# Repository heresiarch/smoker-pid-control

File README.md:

# smoker-pid-control
Arduino based PID Controller with PT1000 elements to control heat in BBQ grill using a blower fan
* PWM Output 0-255 
* Manual controller mode
* PID based controller mode
* Fuzzy based controller mode
* OLED Display
* Adafruit MAX31865 RTD Sensor Breakout module
* Arduino Micro
* Rotary Encoder user interface

# Field Test
## PID Mode
PID Mode works very well with Weber 57 cm BBQ Grill. Only small overshots in the beginning. I use a BBQ Guru Viper Pit 12 V Fan which has no PWM, PWM is converted to linear voltage with a simple Buck converter. PID Values are very much dependend on the type of BBQ Grill. I have a hard cut off rule above 1.0 °C which counters some overshots in the beginning. Autotune experiments are a good waste of time IMHO, better is to use PID values based on experiments. 

## Fuzzy Mode
Fuzzy mode is very stable and gets good steady state for setpoint temperature. Fuzzy mode is controlled by Fuzzyset based on temperature difference. You should change rules sets based on your setup and used MOSFET (RDSon and PWM values). Fuzzy update rate is 5 seconds. I derived a simple fuzzy set from the much more sophisticated example from the link below, which has unfortunately too many rules for my Arduino Micro memory: https://github.com/rvt/bbq-controller/blob/master/lib/bbq/bbqfanonly.cpp.

## Results
Overall I could hold constant temperature of 110 °C over 4 hours with 1 char basket filled with some weber charcoal briquettes, and still had enough of them left for some hours. With 2 char baskets starting on each side with 2-3 hot coals in ignition cord style and with grill fully meat loaded I got superior results in temperature stability with the Fuzzy Sets defined.

## References and similar Projects
* [Smokerduino on Instructables](https://www.instructables.com/id/Smokerduino/)
* [Fuzzy based BBQ Controler Project](https://github.com/rvt/bbq-controller)
* [Small OLED Library ss_oled](https://github.com/bitbank2/ss_oled)
* [Another small OLED Library SSD1306Ascii](https://github.com/greiman/SSD1306Ascii)

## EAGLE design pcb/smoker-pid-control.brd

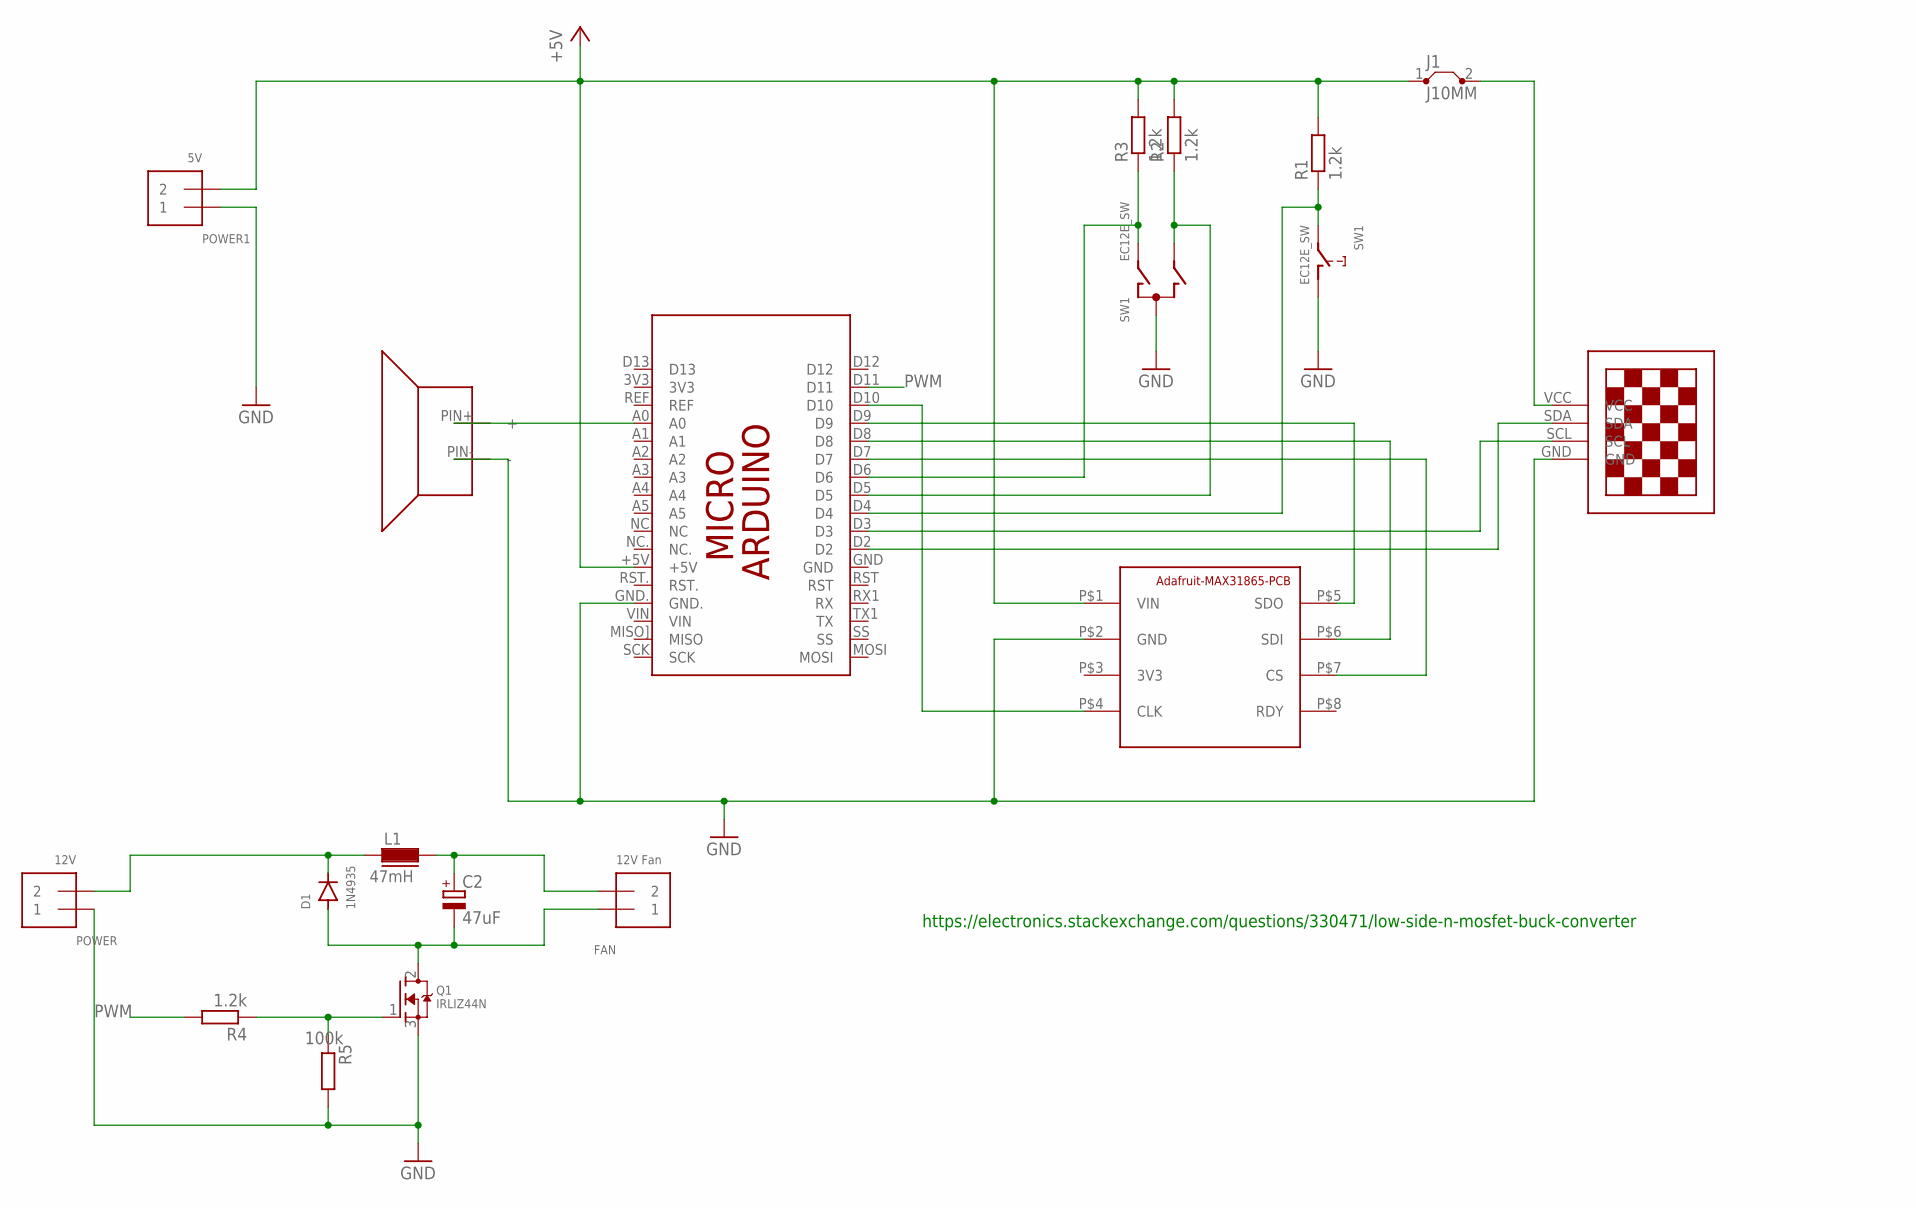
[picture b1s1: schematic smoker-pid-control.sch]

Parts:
C2: 47uF; E5-8,5
D1: 1N4935; DO34-7
FAN: 12V Fan; TERMBLOCK_1X2-3.5MM
J1: J10MM; 10
L1: 47mH; FASTRON_07HCP_INDUCTOR
PCB1: ARDUINO_MICRO
POWER: 12V; TERMBLOCK_1X2-3.5MM
POWER1: 5V; TERMBLOCK_1X2-3.5MM
Q1: IRLIZ44N; TO220V
R1, R3, R4: 1.2k; 0207/10
R2: 1.2k; 0207/15
R5: 100k; 0207/10
SW1: EC12E_SW; ALPS_EC12E_SW
U$1: ADAFRUIT-MAX31865; MAX31865-BRD
U$2: 13"OLED13"OLED; 1.3"OLED
U$3: KC-1206

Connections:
3V3: U$1.P$3 (3V3)
+5V: J1.1, PCB1.+5V, POWER1.2, R1.2, R2.2, R3.2, U$1.P$1 (VIN)
GND: PCB1.GND., POWER.1, POWER1.1, Q1.3 (S), R5.2, SW1.C, SW1.D (1), U$1.P$2 (GND), U$2.GND, U$3.PIN- (-)
unnamed: PCB1.D2, U$2.SDA
unnamed: PCB1.D3, U$2.SCL
unnamed: PCB1.D10, U$1.P$4 (CLK)
unnamed: PCB1.D4, R1.1, SW1.E (2)
unnamed: PCB1.D9, U$1.P$5 (SDO)
unnamed: PCB1.D8, U$1.P$6 (SDI)
unnamed: PCB1.D7, U$1.P$7 (CS)
unnamed: PCB1.D5, R2.1, SW1.B
unnamed: PCB1.D6, R3.1, SW1.A
unnamed: PCB1.A0, U$3.PIN+ (+)
unnamed: C2.+, FAN.2, L1.2
unnamed: Q1.1 (G), R4.1, R5.1
unnamed: J1.2, U$2.VCC
unnamed: C2.-, D1.A, FAN.1, Q1.2 (D)
unnamed: D1.C, L1.1, POWER.2
PWM: PCB1.D11, R4.2

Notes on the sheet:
https://electronics.stackexchange.com/questions/330471/low-side-n-mosfet-buck-converter

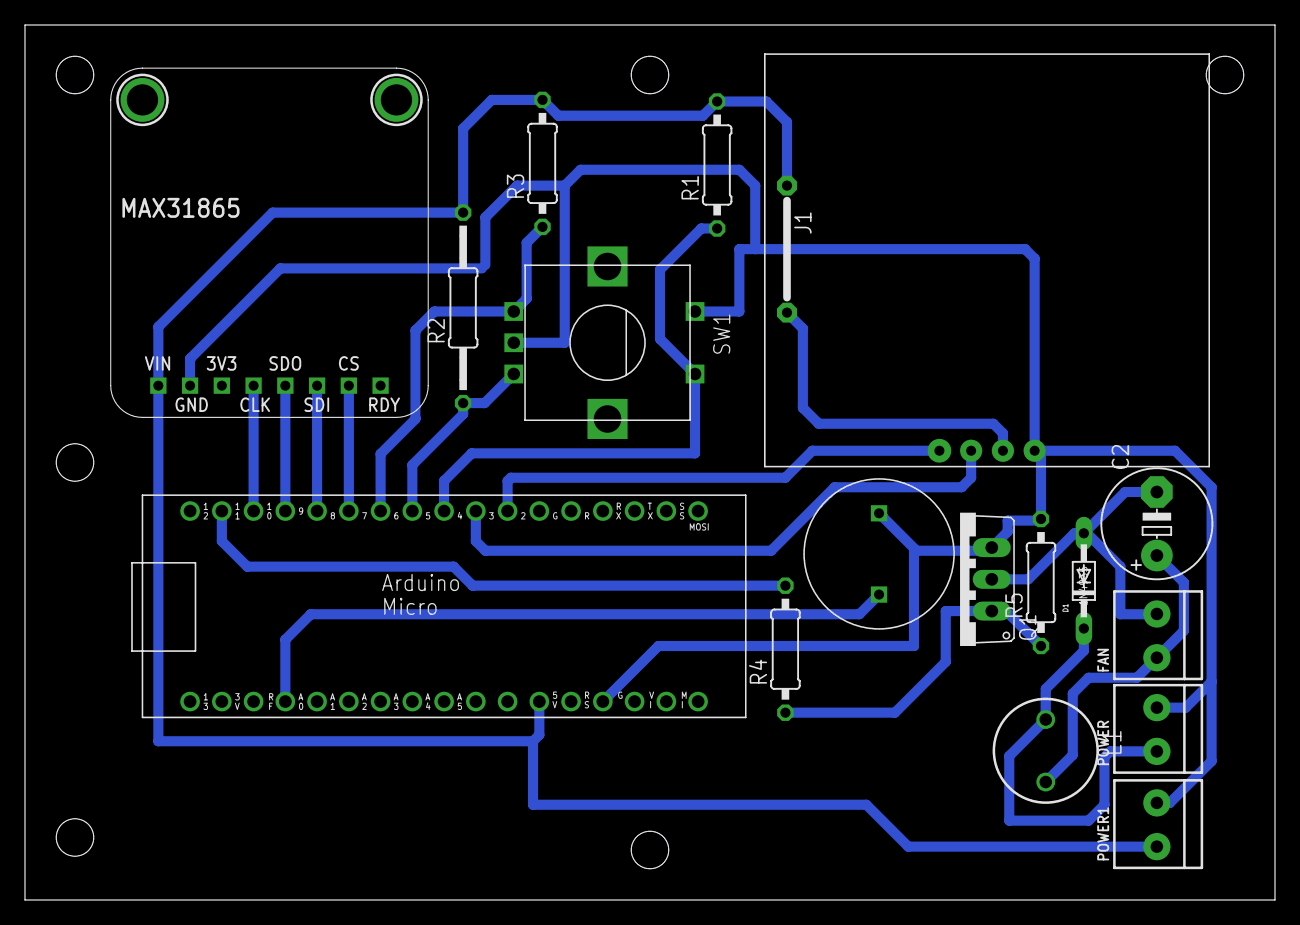
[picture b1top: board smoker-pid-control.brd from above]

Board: 2 copper layers, 100.0 x 70.0 mm, 18 parts (0 on the bottom side), 18 nets.

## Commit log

2020-05-22 first blood
2020-05-22 I love it
2020-05-24 debounce
2020-06-21 state machine
2020-06-21 manual mode
2020-06-26 display PWM in manual mode if changed
2020-06-28 PID Control added
2020-06-29 new PID
2020-06-29 better PID Control
2020-06-29 new delete is not good in arduino
2020-07-02 autotune
2020-07-02 fix state machine
2020-07-02 remove autotune too chaotic
2020-07-05 include alternate fuzzy controller
2020-07-10 fix platformio.ini dependencies
2020-07-12 cleanup
2020-07-17 new OLED display streamline code
2020-07-18 clean and optimize
2020-07-19 implement count down
2020-07-19 fix cosmetics
2020-07-24 save some K of flash for other functions oled lib optimized
2020-07-24 format code
2020-08-02 simplify fuzzy init, avoid multiples new delete
2020-08-02 fix indent
2020-08-02 message tone /alarm
2020-08-03 pwm limits
2021-04-11 eagle pcb
2021-04-11 eagle 2
2021-04-17 pcb with pulldown on gate
2021-04-24 fix drill hole sizes, fix oled wiring bug
2021-04-26 single layer Layout, groundplane fix, stronger airwires
2021-05-01 final pcb
2021-05-04 optimise space
2021-05-06 fix Micro power path from Vin to 5V pin, separate 5V and 12V supply
2021-05-06 update pdf
2021-05-08 final prototype ready
2021-05-08 finished
